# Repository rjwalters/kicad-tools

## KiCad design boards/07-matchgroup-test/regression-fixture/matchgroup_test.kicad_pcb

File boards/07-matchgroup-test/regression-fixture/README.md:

> Historical synthetic routing fixture. These footprints are not an assembled
> product. The working SDRAM redesign is in `../real_design/`. Legacy generators
> remain in the parent directory and default to `../regression-output/`; the
> files here preserve the existing regression witness.

# Match-Group Test Board (Board 07)

Regression testbench for the N-trace match-group routing subsystem
introduced by Epic [#2661](https://github.com/2AMLogic/kicad-tools/issues/2661)
(Phases 1-2).  Demonstrates each match-group scenario the epic was
scoped against (DDR data byte, MIPI CSI lane group, HDMI TMDS lane
group, generic address bus) by routing one or more match-grouped
nets per scenario on a 4-layer JLCPCB tier-1 stackup.

**This is not a working device.**  The source / sink footprints
(QFN-48, BGA-49 simulator, FFC-6, etc.) are synthetic placeholders
chosen to expose realistic escape lengths so the routing algorithm
sees non-trivial group skew to measure / tune.

## Quick Start

```bash
# One-command build (recommended)
kct build boards/07-matchgroup-test

# Or run specific steps
kct build boards/07-matchgroup-test --step schematic
kct build boards/07-matchgroup-test --step pcb
kct build boards/07-matchgroup-test --step route
kct build boards/07-matchgroup-test --step verify

# Run DRC against the committed routed PCB (the fixture in this directory)
kct check boards/07-matchgroup-test/regression-fixture/matchgroup_test_routed.kicad_pcb \
  --mfr jlcpcb \
  --net-class-map boards/07-matchgroup-test/regression-fixture/net_class_map.json
```

## Stackup

4-layer JLCPCB tier-1 (identical to board 06):

| Layer index | KiCad name | Purpose                              |
|-------------|-----------|--------------------------------------|
| 0           | F.Cu      | Signal (escape + outer routing)      |
| 1           | In1.Cu    | GND plane (impedance reference)      |
| 2           | In2.Cu    | PWR plane (+1V2 / +1V8)              |
| 31          | B.Cu      | Signal (optional bottom escape)      |

## Match-Group Scenarios

| Scenario   | Group name           | Members                     | Skew tolerance | Phase features exercised                                                  |
|------------|----------------------|-----------------------------|----------------|---------------------------------------------------------------------------|
| DDR byte   | `DDR_DATA_BYTE_0`    | 9 singles (DQ0-7, DM0) + DQS pair | 0.1 mm    | 1A declaration, 1B tracker, 1C detection, 1D producer, 2E cascade, 2F composition |
| MIPI CSI   | `MIPI_CSI_LANES`     | 3 pairs (CLK, DAT0, DAT1)   | 0.05 mm        | 1A, 1B, 1C, 1D, 2F symmetric serpentine target                            |
| HDMI TMDS  | `HDMI_TMDS_LANES`    | 3 pairs (D0, D1, D2)        | 0.075 mm       | 1A, 1B, 1C, 1D, 2F composition                                            |
| ADDR bus   | `ADDR_BUS`           | 8 singles (A0-A7)           | 0.5 mm         | 1A explicit declaration (also exercises 1C suffix-inference fallback path) |

**4 match groups across 30 paired/grouped nets**.  Combined with
GND/+1V2/+1V8, the board has **33 nets total** --- comparable in
scale to board 06 (26 nets) and well below board 05 (~50 nets).

## Components

| Reference | Description                              | Footprint                                          |
|-----------|------------------------------------------|---------------------------------------------------|
| U1        | QFN-48, 0.8 mm pitch (DDR controller)    | `Package_DFN_QFN:QFN-48-1EP_7x7mm_P0.5mm`         |
| U2        | QFN-48, 0.8 mm pitch (DRAM sink)         | `Package_DFN_QFN:QFN-48-1EP_7x7mm_P0.5mm`         |
| J1        | FFC, 6-pin 1.0 mm pitch (MIPI source)    | `Connector_FFC:FFC_6P_1.0mm`                      |
| U3        | QFN-24, 0.8 mm pitch (MIPI sink)         | `Package_DFN_QFN:QFN-24-1EP_4x4mm_P0.5mm`         |
| J2        | HDMI Type A receptacle (synthetic)       | `Connector_Video:HDMI_A_Receptacle`               |
| U4        | BGA-49 simulator, 1.27 mm pitch          | `Package_BGA:BGA-49_5.0x5.0mm_Layout7x7_P0.5mm`   |
| J3        | 1x9 pin header, 0.1 in pitch (ADDR)      | `Connector_PinHeader_2.54mm:PinHeader_1x09_P2.54mm_Vertical` |
| U5        | QFP-48, 0.8 mm pitch (SRAM-style sink)   | `Package_QFP:LQFP-48_7x7mm_P0.5mm`                |

All sinks placed on F.Cu so all routing happens on the outer signal
layers; GND/PWR planes on inner layers are unencumbered for
impedance reference.

## Per-Group Net Class Declarations

The protocol-specific `NetClassRouting` instances live in
`generate_design.py`:

- `ddr_data_byte_0_net_class()` --- `length_match_group="DDR_DATA_BYTE_0"`,
  `length_match_tolerance_mm=0.1` (DDR commodity tolerance)
- `ddr_dqs_pair_net_class()` --- pair members of DDR group
  + `coupled_routing=True`, `pair_protocol="DDR_DQS_CK"` (UG583 2 ps
  within-pair limit, an error)
- `mipi_csi_net_class()` --- `length_match_group="MIPI_CSI_LANES"`,
  `target_diff_impedance=100`, `pair_protocol="MIPI_DPHY"`
- `hdmi_tmds_net_class()` --- `length_match_group="HDMI_TMDS_LANES"`,
  `target_diff_impedance=100`, `pair_protocol="HDMI_TMDS"`
- `addr_bus_net_class()` --- `length_match_group="ADDR_BUS"`,
  `length_match_reference="A0"` (pace-car semantic)

Within-pair skew is judged against the derived ps budget of the declared
protocol ([guide 09](../../../docs/guides/diff-pairs/09-skew-budget.md)),
with no hand-set `skew_tolerance_mm` cap (Issue #7913): the derived
budget is the only pair skew limit.

`build_net_class_map()` assembles them into a `net_name -> NetClassRouting`
dict that the autorouter (in `route_pcb()`), the JSON sidecar
(`regression-fixture/net_class_map.json`), AND the regression test
(`tests/test_board_07_matchgroup_test.py::test_phase_features_exercised`)
all import.  This ensures test/sidecar/implementation parity.

## Files

Paths below are relative to `boards/07-matchgroup-test/`.  The legacy
generators live in that parent directory; the committed regression
witnesses live here, in `regression-fixture/`.  (`output/` holds the
unrelated real SDRAM-exerciser build --- see `../real_design/`.)

| File                                                   | Description                                           |
|--------------------------------------------------------|-------------------------------------------------------|
| `regression-fixture/project.kct`                       | KCT v1.0 spec (manufacturing/intent metadata)         |
| `generate_schematic.py`                                | Emits the schematic (`matchgroup_test.kicad_sch`)     |
| `generate_pcb.py`                                      | Emits the unrouted PCB + holds NETS / DIFFPAIRS / match-group dicts |
| `generate_design.py`                                   | End-to-end pipeline (schematic + PCB + route + sidecar + DRC); regenerates into `regression-output/` by default, never over the committed fixture |
| `regression-fixture/matchgroup_test.kicad_sch`         | Generated schematic (committed)                       |
| `regression-fixture/matchgroup_test.kicad_pcb`         | Unrouted PCB (committed; the gate's re-route input --- carries #7557's U4 TMDS ball move, see "U4 TMDS ball move" below) |
| `regression-fixture/matchgroup_test_routed.kicad_pcb`  | Routed PCB (committed --- consumed by CI DRC gate)    |
| `regression-fixture/net_class_map.json`                | Sidecar (Phase 3M) consumed by `kct check --net-class-map` |
| `regression-fixture/placement_delta.json`              | Reviewed swap-group pad re-binding (#5537); replayed only via `--placement-delta` |

## DRC Status

The routed PCB is checked against JLCPCB tier-1 rules via:

```bash
kct check boards/07-matchgroup-test/regression-fixture/matchgroup_test_routed.kicad_pcb \
  --mfr jlcpcb \
  --errors-only \
  --net-class-map boards/07-matchgroup-test/regression-fixture/net_class_map.json
```

The `--net-class-map` flag is **mandatory** for the
`match_group_length_skew` rule (Phase 2G #2702) and the diff-pair
rules to fire on the standalone routed PCB --- without the sidecar
they degrade to no-ops (the same trap PR #2692 fixed for diff-pair
rules).

### Initial allowlist budget

Per the curator note on issue #2724, the initial DRC error count is
empirical: route the board, count errors, add ~20% headroom, then
record in `.github/routed-drc-tolerance.yml`.  Phase 3N (#2726) will
tighten iteratively as upstream router improvements land.  (#7367
replaced that count with an identity allowance; see "CI Gate" below.)

## Current targeted repair (2026-09-09)

The committed routed board connects **27/31 signal nets**, including all six
MIPI nets. It remains **partial and unsuitable for manufacturing sign-off**:
`DQ3`, `DQ4`, `TMDS_D0_N`, and `TMDS_D1_N` are open. Native KiCad DRC, with
refilled zones and the original project/rules, reports four unconnected items,
zero other errors, and 31 warnings. `kct check` reports eight errors: those four
opens and the remaining DDR/HDMI pair skew and continuity failures. All three
MIPI pairs and their match group pass the authored electrical checks.

The repair rotates J1 to -90 degrees at the same location, reroutes only MIPI,
and preserves the other copper. MIPI and HDMI width is resolved to 0.225 mm at
the authored 0.100 mm gap (102.3 ohm model, within the authored 100 ohm ±10%
target). DQS remains at its authored 0.150/0.100 mm width/gap. No net mappings,
pair/group constraints, or checks were removed; no waivers were added.

Reproduce the targeted repair in a separate directory:

```sh
uv run python boards/07-matchgroup-test/repair_mipi.py /tmp/board07-repair
```

The script accepts `--input PATH` for a previous routed artifact, sets J1's
absolute orientation, disables the routing cache, runs coupled MIPI routing,
then tunes pair skew and a common six-route length target while enforcing
partner clearances. It saves the full sidecar, tuning results, route log,
native DRC, and full `kct check` report. Exit status 2 reflects the board's
remaining errors. The generator exposes this J1 orientation as an optional
argument; its default placement and routing map stay historical because a fresh
full-board generation/routing run has **not** been measured with this change.
Fixed-gap width sizing is explicitly selected by the repair script;
the committed result comes from the targeted repair of the historical board.
See [the experiment record](../diagnostic-runs/astra-j1-orientation.md).

## Historical routing plateau (before 2026-09-09 repair)

The following measurements describe the previous committed artifact and the
earlier full-board routing recipe. That board connected
**26/31 signal nets** (~83.9% by net count); its
`output/lvs.json` recorded `clean: false` with exactly **5 open
copper mismatches**. The gallery rendered board 07 as `partial`/`lvs`
(the audit was real:
`copper_bound_pad_count: 244`, `copper_vacuous: false` --- cf. #4011).

### The 5 opens

| Net | Pad A | Pad B | Bundle |
|-----|-------|-------|--------|
| `DQ3`         | U1.28 | U2.4  | DDR data byte |
| `DQ4`         | U1.32 | U2.8  | DDR data byte |
| `MIPI_DAT0_N` | J1.4  | U3.4  | MIPI CSI |
| `TMDS_D0_N`   | J2.2  | U4.B2 | HDMI TMDS |
| `TMDS_D1_N`   | J2.5  | U4.B4 | HDMI TMDS |

This is the same set re-measured by the #4049 epic dossier; the older
#3438 thread cited a 3-net subset before the board was re-spun.  Three
verifiers agree on this exact set: `kct net-status --why`,
`output/lvs.json` (`copper_mismatches`), and the KiCad cross-gate
`kicad-cli pcb drc --refill-zones` (5 unconnected pads at the same five
pads).

### Decision: correct HDMI widths while preserving the witness (#5126)

**Recommendation:** permit one explicit, reviewed width correction to this
historical fixture. Retarget existing `TMDS_*` track widths from 0.375 mm to
`HDMI_TMDS_LANES`' declared 0.225 mm, preserving their centerlines, layers,
net assignments and vias. The fixture exists to retain match-group skew geometry
and documented routing defects; a stale width contradicting its own sidecar is
not an additional defect we need to preserve. This does not make the synthetic
board a release artifact or remove its known opens.

The September 12 investigation on #5126 reported matching before/after DRC
error signatures after native refill and an unchanged angle census of 841
segments, including 12 off-angle segments. It also reported that stripping and
rerouting all six TMDS nets reduced their connected count from four to one.
Those are prior experimental results, not acceptance evidence for a future
commit. **A full strip-and-reroute is not proposed.** The present saved fixture
has 0.375 mm segments on the four routed TMDS nets; the two documented open
TMDS nets have no routed segments to retarget.

The alternative is to freeze every byte forever. That preserves the original
hash but leaves the fixture internally inconsistent and teaches readers the
wrong relationship between the sidecar and saved copper. A narrowly documented
exception with measured invariants better preserves the witness's purpose.
The original bytes remain identifiable by SHA256
`ab3a2c2d4aea466f828e540189ac851ddb8c41505c8185be65924ec5ff92a9a6`
and by repository history.

**Implementation gate:** after review of this decision, a separate #5126 PR
must add the width-retarget path to `repair_hdmi.py` and publish its exact
before/after evidence. It must preserve non-TMDS track geometry, all pad/net
identities, vias and authored constraints; `DDR_DQS` is outside this change.
Before promotion, compare native and analyzer pad components and open identities,
not just aggregate counts, and compare DRC error signatures with the original
project/rules and sidecar after native KiCad 10 zone refill. Narrower tracks can
lose a marginal copper contact even when their centerlines are unchanged, so
connectivity must be measured rather than assumed. Retain the original input,
refilled candidate, commands, KiCad identity and hashes for reproduction.
The known-current four-open set above must not be confused with the five-open
historical table, which predates the MIPI repair.

Update `HISTORICAL_WITNESS_SHA256` in `tests/test_fleet_45_census.py` only in the
same implementation commit as the accepted PCB, with a comment citing #5126.
Keep the exact `(841, 12)` angle-census assertion and exercise the match-group
skew checks; do not remove the witness pin or relax its regression gates.
This decision note changes neither PCB bytes nor their hash pin. If independent
review rejects the exception, retain the frozen witness and close #5126 with
that recorded rationale.

### HDMI width correction (2026-09-15, #5126)

The reviewed exception above is applied to **35 width atoms** on the four routed
TMDS nets: `TMDS_D0_P`, `TMDS_D1_P`, `TMDS_D2_N`, and `TMDS_D2_P`, from 0.375 mm
to the sidecar's 0.225 mm. The two open TMDS nets have no track segments.
Every other byte of the saved PCB is unchanged, including segment centerlines,
vias, existing zone fills, and non-TMDS widths. DQS copper is unchanged; this
correction does not establish its agreement with its authored width.

The old PCB SHA256 is recorded in the decision above; the corrected saved PCB is
`fb58581eba53bb9f1dfe33a278fb896b2f08b5f4fc2e82211124d8586ba7aaf0`.
Its hash pin was updated with the PCB, retaining the exact 841-segment,
12-off-angle census. The change is a regression-fixture correction, not a
manufacturing release.

Current-source before/after checks retain the same four open nets and exact
native pad components. Native KiCad 10.0.6 reports four unconnected items,
zero other errors and 31 warnings on each input with native refill enabled.
The current Python checker reports **13 errors, 22 warnings and 12 unique
error rule/net signatures** on both saved inputs, including existing
via-in-pad findings. These are current measurements; the earlier eight-error
account above describes the September 9 check. Match-group checks remain
engaged, and no error severity or allowance was changed.

The [retained component and signature record](hdmi-width-correction-5126.json)
contains the shared exact pad partitions/open identities and all four measured
PCB hashes. Saved and separately refilled before/after copies pass the same
comparisons. Native refills are evidence copies; the committed PCB retains its
original fill bytes so unrelated serialization and geometry remain untouched.

Reproduce from the original fixture in a fresh directory (use a Python with
`pcbnew` for `--native-python`, and a KiCad 10 `kicad-cli` on `PATH`):

```sh
mkdir /tmp/board07-original
git archive bcaf28ad3399d97df5b0d6cfefe8db7856abc689 \
  boards/07-matchgroup-test/regression-fixture | tar -x -C /tmp/board07-original
uv run python boards/07-matchgroup-test/repair_hdmi.py /tmp/board07-hdmi-width \
  --input /tmp/board07-original/boards/07-matchgroup-test/regression-fixture/matchgroup_test_routed.kicad_pcb \
  --native-python python3
```

A completed preservation check reports `validated historical width correction`
in `evidence.json` and exits **2**, retaining the board's existing errors.
Failure raises an error and records `FAILED`; it is not a promotable candidate.
The script retains the original input, byte-minimal candidate, separate native
refills, reports and command logs. It also supports an already-correct input
without further width edits. The current script was verified from the original
fixture; the contact-loss negative test separately proves that a narrower
track losing a real connection is rejected.

### ADDR_BUS retune (2026-10-18, #6730)

`kct retune-lengths --group ADDR_BUS` re-applied the existing match-group tuner
to the saved fixture (only `A4` and `A6` changed; all other nets, vias and
pads are unchanged). ADDR_BUS skew went from **1.0998 mm to 0.0169 mm** (limit
0.5 mm), measured by `kct check` and by `kicad-cli` per-net lengths
(`test_addr_bus_lengths_match_kicad_cli`). The new meanders sit on In1.Cu, so the
zones were refilled with `kct zones fill`; without the refill the stale GND fill
reports six `clearance_segment_zone` errors. Error signatures are otherwise those
of the previous fixture minus the ADDR_BUS skew finding (`diffpair_length_skew` 5,
`via_in_pad` 5, `connectivity` 4). The census is now `(849, 12)` and the PCB
SHA256 is `fdbb69fd1cae5ee76a6a66788feebfed3490f090652df75fdbf04e864f3df83e`.
The input hash and per-net before/after lengths were recorded by the retuner's
provenance record. Earlier sections describe the pre-retune bytes.

### Placement-delta feedback (#4468, epic #3438 Phase 3)

> **Off since #6448.** The recipe now routes on the lattice engine, and the
> loop's probes re-route with the grid negotiated router, so
> `PLACEMENT_DELTA_FEEDBACK` is `False`. The lattice route reaches 31/31,
> so the loop would have nothing to probe. This section records the grid
> recipe's measurements.

The route step runs `kct route --placement-delta-feedback
--placement-delta-feedback-budget 2 --placement-delta-feedback-timeout
600` (wired from the `PLACEMENT_DELTA_FEEDBACK*` constants at the top of
`generate_design.py`).  Since #5266 the surrounding budget contract is
stated as two separate numbers: `--search-timeout 600` bounds each
individual search stage (the initial negotiated pass), while `--timeout`
carries the **hard total** invocation deadline, derived as
`600 + 2x600 + 600 = 2400 s` (one search stage, one probe allocation per
budget unit, and a postprocessing reserve).  The probe allocation does
**not** escape the total deadline -- it is clamped to whatever the total
has left -- so the total must be large enough to contain both probes or
the out-of-process supervisor kills the run mid-probe and leaves only
unverified partial artifacts.  Each iteration classifies the **routed**
board,
translates every `PLACEMENT_BOUND` / `CONGESTION_SATURATED` diagnosis into
one concrete placement delta, applies the top unprobed one, re-routes, and
keeps it only when the re-route **strictly increases the routed-net count
AND does not increase the router's clearance-violation count** ---
otherwise placement, router pads, routes and the routing grid revert
atomically.

**Measured verdict: the reach stays at 26/31, and that is a decision, not
a failure to find anything.**  Solo, seed 42, C++ backend built,
`PYTHONHASHSEED=42`, the loop emits a delta for every one of the 5 open
nets and probes the top two.  The probe-level routed counts are
**host-specific** (see "Host-vs-CI divergence" below); both are recorded:

| # | Probe | Routed (host) | Routed (CI, both runs) | Clearance violations (host) | Verdict |
|---|-------|---------------|------------------------|-----------------------------|---------|
| 0 | `U2` `rotate_180` --- from `DQ3`'s `DE_REVERSE_BUNDLE` verdict | 25 -> **16** | 25 -> **14** | 0 -> **1489** | reverted (reach collapse) |
| 1 | `U3` translate `(-0.77, -1.85)` mm --- from `MIPI_DAT0_N`'s `MOVE_PART` | 25 -> **26** | 25 -> **25** | 0 -> **2** | reverted (host: clearance; CI: no reach gain) |

The `Routed` columns are the loop's internal routed-net counter, whose
baseline at probe time is 25/31; the `26/31 -> 27/31` figures in the
prose below are the same host-measured +1 net expressed as final-artifact
reach (the probe-1 artifact measured 27/31 on that host).

Probe 0 is the informative negative result.  The classifier is **right**
that the DDR byte is reversed at `U2` --- it measures 28/28 facing pad
pairs inverted between `U1` and `U2` --- but a 180-degree rotation is not
the move that fixes it: it de-reverses the pad ORDER while relocating the
whole facing column to the *far* side of the package, so the byte then has
to wrap around a 7x7 mm QFN.  Reach collapses to 16/31.  The
geometrically correct move is a **mirror** of the pad column, which KiCad
expresses only as a layer flip and which the Phase-1 translator therefore
never emits.

Probe 1 is the real finding --- **on the local macOS arm64 host**.  There,
a single bounded 2 mm translate of `U3` **does** close `MIPI_DAT0_N` ---
26/31 -> 27/31 --- but the extra copper it lets into the DDR channel costs
manufacturability.  This is a host-specific measurement, not a universal
one: both independent CI runs (ubuntu-latest, same seed and
`PYTHONHASHSEED`) measured the same probe as routed **25 -> 25** --- no
reach gain --- so on CI the delta is refused for lack of a strict
routed-net increase and the clearance-regression guard never fires.  The
manufacturability cost below was measured on the host's 27/31 artifact:

* two segment-to-pad clearances drop under the jlcpcb floor
  (0.076 mm and 0.094 mm against a 0.102 mm minimum, at the `U1` DDR
  escape), taking blocking DRC from 10 to 13 on the same host; and
* the `ADDR_BUS` length-match tuner, which normally drives that group's
  skew to **0.000 mm**, is left at **11.03 mm** --- a
  `match_group_length_skew` error on the very board that exists to
  exercise that rule.

Shipping it would have required widening
`.github/routed-drc-tolerance.yml`'s board-07 floor from 8 to 13.  Trading
a DRC allowlist widening for one net is not an improvement on a
match-group/DRC testbench, so the loop's acceptance test now requires
*both* a reach gain and no clearance regression, and this delta is
refused.  The refusal is recorded, with its measurements, in
`output/matchgroup_test_routed_placement_delta.json` (the `reverted`
section carries `routed_before` / `routed_after` and `revert_reason`) so
the decision is auditable rather than invisible.

**The acceptance test is *relative*, and #4770 measured what that costs.**
`PlacementDeltaFeedbackLoop.run_delta` keeps a delta on
`new_count > pre_count` --- a comparison against the reach the loop
currently holds, not against an absolute floor.  So anything that
*depresses* the initial negotiated pass's reach also lowers the bar this
probe has to clear.  Issue #4770's A/B is the worked example: with the
relief-rescue sub-search bound switched from its 10 s wall clock to the
deterministic per-net expansion cap (#4730's withdrawn flip), the
negotiated pass completes 2 rip-up iterations instead of 5 and enters the
loop at 24/31 instead of 26/31 --- and *on CI* this same `U3` translate
then measures 23 -> 27, clears the gate, and is **kept**, taking blocking
DRC from 8 to 13 with exactly the 0.076 / 0.094 mm `U1`-escape clearances
and the 11.03 mm `ADDR_BUS` skew described above.  The `+1 net` in that
measurement is this delta, not a router improvement.  Full journal:
`diagnostic-runs/README.md`, section "Deterministic relief-rescue bound:
A/B measurement (#4770)".

Two useful side effects of running the loop, both measured on the same
host:

* the delta artifact is emitted on **every** run, so the classifier's
  per-net proposal for each open net is a build output rather than a
  one-off investigation; and
* blocking DRC on the shipped artifact measures **8** (equal to the
  committed allowlist floor) versus **10** for a loop-off local regen ---
  the loop's atomic revert now also rebuilds the routing grid, which the
  post-loop optimize/DRC-nudge stages read.

The shipping budget is **2**: probe 0 is the classifier's top-ranked rung
and probe 1 is the one that is only marginally short of acceptable, so if a
future router change removes those two clearances the loop will take the
net automatically.  A direct consequence: `DQ4`, `TMDS_D0_N` and
`TMDS_D1_N` are **unprobed-by-budget, not unroutable** --- the loop
proposes a delta for each of them (all proposals are recorded in the
delta artifact; CI logs `Deltas proposed: 10`), but the budget of 2 is
consumed by `DQ3`'s and `MIPI_DAT0_N`'s probes before those three are
ever tried.  Their `CONGESTION_SATURATED` / `PLACEMENT_BOUND` verdicts in
the table below describe why the *router* leaves them open at the current
placement; no placement delta for them has been probed and refused.  Each
budget unit costs one complete board-07 re-route; the whole route step
measures **27m05s** locally against ~16 min for the loop-off recipe.

#### Host-vs-CI divergence (probe-level only)

The probe-level routed counts above are host-dependent even at a fixed
seed.  Same code, `--seed 42`, `PYTHONHASHSEED=42`:

* local macOS arm64 host: probe 0 routed `25 -> 16`, probe 1 routed
  `25 -> 26` (reverted for clearance);
* CI ubuntu-latest: probe 0 routed `25 -> 14`, probe 1 routed `25 -> 25`
  (reverted for no reach gain) --- reproduced **bit-for-bit across two
  independent CI runs** on different head SHAs (PR #4556; run
  `30680605924` and its predecessor).

The *decisions* and the final state agree everywhere: 10 deltas proposed,
0 kept, exit `pd_reverted`, 26/31 reach, the identical 5-net open set,
and blocking DRC 8 at the committed floor.  Only the probe-level
narrative diverges.  This is the same honesty hazard as board-06's
run-to-run nondeterminism (#4536), on a cross-host axis: future
threshold or known-open decisions for this board should be made against
the CI numbers.

#### Mirror probe (#4560) --- first measurement

`DE_REVERSE_BUNDLE` now proposes `kind="mirror"` (a KiCad-semantics
layer flip of `U2` about its own anchor) instead of `rotate_180`, so
probe 0 of a fresh run is the mirror.  The structural diagnosis is
unchanged and still correct --- 28/28 facing pad pairs invert between
`U1` and `U2`, and a flip is the only orientation move that can
un-reverse a mirrored pin order (rotate_180 preserves chirality).

First measurement, **host-qualified per the divergence note above**
(macOS arm64, solo, `--seed 42`, `PYTHONHASHSEED=42`):

* probe 0 `U2` **mirror**: routed `25 -> 23`, clearance `0 -> 69`,
  reverted.  The flip moves `U2`'s pad column to `B.Cu`, which
  un-reverses the bundle *ordering* but relocates the entire DDR escape
  problem to the back side, where the routed baseline's copper and the
  skipped power fanout already live --- reach drops and the
  clearance-regression gate fires.  For calibration: the rotate_180 it
  replaces measured `25 -> 16` on this host (`25 -> 14` on CI), so the
  mirror is the better probe of the two, but neither survives.
* probe 1 `U3` translate: routed `25 -> 26`, clearance `0 -> 2`,
  reverted --- the same host-only marginal keep/refuse case documented
  above, refused again by the clearance gate.

Final state is bit-identical in shape to the committed baseline: 10
deltas proposed, 0 kept, exit `pd_reverted`, 26/31 reach, the identical
5-net open set (`DQ3`, `DQ4`, `MIPI_DAT0_N`, `TMDS_D0_N`, `TMDS_D1_N`).
The atomic revert (placement + router pads + routes + grid, now
layer-aware) restored the board exactly; the delta artifact records both
refusals with `routed_before`/`routed_after` and `revert_reason`.  CI
numbers for the mirror probe should be recorded from this change's
board-07 e2e job when available.

### Netlist write-back from a committed delta (#5537, Epic #5511 Phase 2b)

`regression-fixture/placement_delta.json` is a **committed, reviewed**
placement-delta artifact carrying the declared `DDR_BYTE0` swap group's
crossing-minimising pad re-binding for `U2` (`crossings_before: 28` ->
`crossings_after: 0`, measured by the #5522 proposer against
`matchgroup_test_routed.kicad_pcb` + `net_class_map.json`).  It is the
same `{pad_number: new_net_name}` payload
`kct net-status --why --format json` reports; the deltas were promoted
from the classifier's `proposed` list into the artifact's `applied`
section by that review, and **nothing replays `proposed` automatically**.

The recipe consumes it via `PlacementDelta.from_dict` and applies the
`pad_map` to **both** generated views *before* routing, so the swap
survives a full regeneration and the schematic/PCB still agree pad-for-pad
(a one-sided swap would surface as an LVS mismatch on every re-bound pad):

```sh
uv run python boards/07-matchgroup-test/generate_design.py /tmp/board07-swap \
  --placement-delta boards/07-matchgroup-test/regression-fixture/placement_delta.json
```

The run prints the change report (target, kind, source action, the
`crossings_before`/`crossings_after` evidence and every `pad -> net`
binding) and writes it to `placement_delta_applied.txt` next to the
regenerated artifacts.  `generate_schematic.py` and `generate_pcb.py`
accept the same flag for a single-view regen; `--step route` does not
(it consumes an already-generated PCB and says so).

**Opt-in only.** With the flag absent every generated byte is what it was
before #5537, so the committed witnesses in this directory are unaffected
and are **not** regenerated by that change: the historical open set, the
routed-DRC allowlist floor and the angle-census pin below all still
describe the board that is committed here.  Re-binding `U2`'s DQ pads
changes which nets the router must reach, which would invalidate every one
of those measurements, so promoting a swapped board to the committed
fixture is a separate, separately-measured decision.

The re-binding touches only the eight **declared** `DDR_BYTE0` members
(DQ0-DQ7 on `U2` pads 1-4 / 8-11).  `DM0`, `DQS_P` and `DQS_N` are
`DDR_DATA_BYTE_0` match-group siblings that are deliberately **not**
declared swappable and stay fixed, and no `ADDR_BUS` net is touched at
all.

### Fresh per-net verdict (`kct net-status --incomplete --why`)

Measured on the committed routed PCB and reproduced by a from-scratch
seed-42 re-route (`PYTHONHASHSEED=42 generate_design.py --step route
--seed 42`), which lands on the **identical** 5-open set and the same
classification:

```
Stuck signal nets: 5
  ESCAPE_BLOCKED:       0
  CONGESTION_SATURATED: 2
  BUDGET_STARVED:       0
  PLACEMENT_BOUND:      3
  POUR_DISCONTINUOUS:   0
```

| Net | Verdict | Evidence |
|-----|---------|----------|
| `TMDS_D0_N`   | `CONGESTION_SATURATED` | pad reachable (360 deg lane) but boxed in by committed strict copper (nearest blocker 1.000mm); ripping it would strand `TMDS_D0_P`, `TMDS_D1_P` (1:1 trade) |
| `TMDS_D1_N`   | `CONGESTION_SATURATED` | boxed in (nearest blocker 0.975mm); rip would strand `TMDS_D1_P`, `TMDS_D2_P` (1:1 trade) |
| `DQ3`         | `PLACEMENT_BOUND` | dense cluster (24 foreign obstructions, nearest strict blocker 0.800mm) --- a part must move |
| `DQ4`         | `PLACEMENT_BOUND` | dense cluster (30 foreign obstructions, nearest strict blocker 0.047mm) --- a part must move |
| `MIPI_DAT0_N` | `PLACEMENT_BOUND` | dense cluster (39 foreign obstructions, nearest strict blocker 0.800mm) --- a part must move |

The key signal: **0** nets are `BUDGET_STARVED` (which more router
iterations/wall-clock would fix) or `ESCAPE_BLOCKED` (which corridor
reservation would fix).  Every stuck net is either the diagnostic's own
"a part must move" `PLACEMENT_BOUND` verdict (3/5) or a
`CONGESTION_SATURATED` 1:1 trade (2/5) where ripping the stuck net simply
strands its diff-pair partner --- the N-1 invariant #3438 first
documented.

### What was attempted this pass (v0.16.0 router)

A fresh seed-42 route with the current v0.16.0 router (region-bounded
routing, ampacity net-class, and the post-#4049 hardening all now on
`main`, C++ backend built) was run end-to-end.  The negotiated router's
relief-rescue phase explicitly reported **`Relief rescue resolved 0/5
net(s)`**: for each stuck net it either found no relief path, or found a
path that displaced victims it could not re-land (rolled back under the
no-net-loss guarantee).  The best-so-far routed state (26/31, 0 clearance
violations, 0 overflow) is identical in open-set to the committed
artifact, so the committed artifact remains the shipping truth and is
left unchanged (regen diverges only in trace geometry/UUIDs, not in which
nets close).

### Track A bundle-plan allocator — measured seed-42 verdict (#4257, A4)

Track A (#4252) built the "joint bundle corridor allocation" fix named
below as the genuine remedy for the `CONGESTION_SATURATED` TMDS 1:1
trades: an **atomic diff-pair rip-up/relief transaction** (A2, #4255) so a
committed "P-routed / N-stranded" state is unrepresentable, plus a
**discrete `BundlePlan` allocator with HARD (foreign-net keep-out) per-member
lane reservation** (A3, #4256).  A4 (#4257) wired both through all three
negotiated entry points (`route_all`, `route_all_negotiated`,
`TwoPhaseRouter`) behind the default-OFF `--bundle-river-planner`
(`enable_bundle_river_planner`) flag and ran the board-07 acceptance gate.

**Honest outcome: the TMDS opens do NOT close; the residual is
placement-bound.**  A solo seed-42 A/B on one host (C++ backend built,
`--deterministic-budget`, `PYTHONHASHSEED=42`) measured:

| Run | Reach | Open set |
|-----|-------|----------|
| flag **OFF** (default / shipping) | **26/31** | `DQ3`, `DQ4`, `MIPI_DAT0_N`, `TMDS_D0_N`, `TMDS_D1_N` |
| flag **ON** (`--bundle-river-planner`) | **23/31** | the 5 above **+** `MIPI_CLK_N`, `TMDS_D0_P`, `TMDS_D1_P` |

The reason is the load-bearing A3 finding, now re-confirmed against the
committed placement: the allocator returns the HDMI TMDS bundle
**FEASIBLE with 6 trivial in-order OUTER lanes and 0 via-hops** — the two
facing rows (J2 / U4) carry `D0..D2` co-oriented, so there is **no
forced-crossing contention for the allocator to resolve**.  Reserving the
resulting HARD lanes (12 keep-out lanes / 3780 grid cells across the TMDS
and MIPI bundles) therefore does not open the stuck TMDS N-legs; it only
walls off cells the congested single-ended negotiator needed, stranding
the *partners* (`TMDS_D0_P`, `TMDS_D1_P`, `MIPI_CLK_N`) — a **regression**,
not a gain.

Conclusion: `TMDS_D0_N` / `TMDS_D1_N` are **`PLACEMENT_BOUND`**, not
coupling-contention-bound.  No HARD-lane reservation closes them; the
residual is the same "a part must move" limit as `DQ3` / `DQ4` /
`MIPI_DAT0_N`, tracked under **Track B / #4253** (placement rework).  The
board-07 reach is therefore **unchanged at 26/31** and **the committed
routed artifact is not refreshed** (the flag stays OFF by default and
flag-off is byte-identical to pre-A4 `main`).  Track A still ships its
real deliverable — the general, verified coupled-bundle capability (atomic
pair transaction + discrete allocator + HARD lane reservation, exercised
end-to-end from all three negotiated entry points in
`tests/router/test_bundle_plan_three_path_integration.py`) — available for
future geometries where a bundle *is* crossing-contended, behind the
default-OFF flag so production routing is unperturbed.

### Required class of fix (follow-up, out of scope here)

None of the four gaps is a knob the single-ended negotiated router can
turn today:

- **`PLACEMENT_BOUND` (DQ3, DQ4, MIPI_DAT0_N)** --- the diagnostic's
  verdict is literally "a part must move."  Resolving these requires a
  **placement rework** of the U1/U2/U3/U4/J1/J2 cluster, a separate and
  larger design change (out of scope per this board's charter; see
  #4049).
- **`CONGESTION_SATURATED` 1:1 trades (TMDS_D0_N, TMDS_D1_N)** ---
  ripping the stuck net strands its pair partner.  The genuine fix is
  **joint bundle corridor allocation** (route the whole HDMI/DDR/MIPI
  bundle's escape channel as a coupled group rather than net-by-net),
  the crossing-aware river-routing planner explored and deferred in
  **#3673**, and the CoupledPathfinder budget rework noted under #4049.

The exhaustive knob matrix (iterations, seed, monte-carlo,
differential-pairs, micro-via-in-pad, grid 0.1, two-pass pre-route,
targeted-ripup) was already swept to exhaustion in **#3438** without
reaching 31/31; the 11-net DDR bundle fails 2/11 *alone* on an empty
board.  The board-07 router epic **#4049** re-confirmed this and closed
at plateau.  This pass (#4235) re-validates that verdict against
v0.16.0.  The joint-corridor + placement-rework follow-up is tracked in
**#4243**.

Gap 2 (diff-pair length-skew / routing-continuity quality errors on the
pairs that *are* routed --- DQS/MIPI_CLK/MIPI_DAT1/TMDS_D2) is a
different root cause (pairs routed as independent single-ended traces),
tracked under #4049, and is deliberately **not** touched here.

## Phase 3 Dependency: #2723 (`--length-match-groups`)

The `apply_match_group_tuning` orchestrator + `--length-match-groups`
CLI flag are introduced by **Phase 3H (#2723)** and have NOT yet
landed on `main` at the time of this board's scaffolding.

What works today (Phases 1A/1B/1C/1D + 2.5G):

- `length_match_group` net-class field is declared on every group
- `detect_match_groups` consumes the declarations during routing
- `_finalize_routing` populates `MatchGroupTracker` with measured
  per-group skew (post-route)
- `match_group_length_skew` DRC rule fires when the sidecar JSON
  is loaded into `kct check`

What is deferred until #2723 lands:

- Group-level meander insertion to actively REDUCE skew (only
  measurement happens today)
- AC#7's "post-pass skew strictly less than pre-pass skew" check
  for the DDR data byte (today's pre-pass and post-pass skews
  are identical because no tuning step runs)

Status update: #2723 has since landed and is closed. `route_pcb` in
`../generate_design.py` now passes `--length-match-groups` (#3098), so
the deferral described above is historical. The `# TODO Phase 3H
(#2723)` comment that remains there asks only to verify that the flag
consumes the `net_class_map.json` sidecar.

## CI Gate (Phase 3N, #2726)

This board is consumed by the **Phase 3N CI gate** (issue #2726),
which lives at `.github/workflows/ci.yml::matchgroup-routing-regression`.
The gate is a sibling of the `diffpair-routing-regression` job (board
06) and runs on every PR to `main`.  Contract:

1. Re-routes board 07 from scratch with
   `python boards/07-matchgroup-test/generate_design.py --step route --seed 42`.
2. Asserts every blocking DRC finding is listed **by identity** (rule +
   pair, net or match group, each with an open tracking issue) in
   `MATCHGROUP_FIXTURE_ALLOWED_FINDINGS` / `MATCHGROUP_ALLOWED_GROUPS` in
   `scripts/ci/check_matchgroup_coverage.py`, and that every listed entry
   still fires (a fixed finding fails the gate as stale until its entry
   is deleted).  The board has no entry in
   `.github/routed-drc-tolerance.yml`, so the count of blocking findings
   *outside* the allowance must be 0
   ([#7367](https://github.com/2AMLogic/kicad-tools/issues/7367); the
   old count, ratcheted 35 -> 14 -> 9 -> 8, let a new finding hide
   behind a fixed one).  Advisory `connectivity` is not blocking; reach
   is gated by item 4.
   <!-- kct:doc-pin drc-tolerance boards/07-matchgroup-test/regression-fixture/matchgroup_test_routed.kicad_pcb = 0 -->
   The claim above is machine-checked by `kct check --only doc_drift`
   (issue #4540): ratcheting the yml without updating this README
   trips `doc_drift_stale_pin`.
3. Asserts the `match_group_length_skew` DRC rule was actually
   exercised --- i.e., `rules_checked_by_rule["match_group_length_skew"] >= 1`
   in the `DRCChecker` summary.  Without this assertion a regression
   that disables match-group detection (e.g., a future change that
   breaks `derive_group_skew_data` or unwires `length_match_group`
   from the net classes) would silently produce a 0-violation report
   and hide the defect.
4. Asserts signal reach (Issue #7319): at least `REQUIRED_SIGNAL_REACH`
   (31 since #7557) of the 31 non-pour nets are complete per `NetStatusAnalyzer`,
   the same counter board 06's gate uses.  Below it the gate exits 2 and
   names the open nets.  The committed 27/31 routed artifact in this
   directory is below the contract on purpose; it is the witness that
   the assertion bites (`--skip-route` against it fails).

### Lattice recipe (Issue #6448, slice 1)

The recipe routes with `--route-engine lattice --strategy basic` (plus the
unchanged `--differential-pairs`, `--tighten-diffpair-gap`,
`--length-match-groups`, `--deterministic-budget`, seed 42). The grid
`--strategy negotiated` run and its placement-delta loop are gone. Measured on
main `1388d4190` (native build 65, `PYTHONHASHSEED=42`, pinned KiCad 10.0.6
image, `--refill-zones`):

| check | lattice recipe |
|---|---|
| pairs coupled | 7/7 |
| signal reach / copper-LVS | 31/31; 0 shorts / 0 opens over 244 pads |
| pair skew | DQS 0.260 mm (1.454 ps of 2.00 ps); MIPI_CLK/DAT0/DAT1 and TMDS_D0/D1/D2 0.000 mm |
| group skew | DDR_DATA_BYTE_0 0.001 mm; MIPI_CSI_LANES 0.000 mm; HDMI_TMDS_LANES 0.000 mm |
| `kct check --mfr jlcpcb` | 0 errors |
| kicad-cli DRC | 0 errors, 0 unconnected; the same 24 warnings as grid |
| `check_board07_diffpair_baseline.py` | copper_safety 0, opens 0, skew_out_of_range 0 |
| `check_matchgroup_coverage.py --seed 42` | exit 0, 0 unallowed errors |

The route step runs about 1 min, against about 27 min for the grid recipe.
Its derived `--timeout` drops from 2400 s to 1200 s because there are no
probe allocations.

### Re-route reach (seed 42, Issue #7319)

The gate's seed-42 re-route reaches **31/31** since #7557 (see "U4 TMDS
ball move" below); before it, **30/31** (`TMDS_D0_N` open) with 0
placement-delta probes.  #7163 briefly dropped it to 29/31: the DDR strobe
pair carried no impedance target, so the router synthesized 100 ohm from
the validator's `.*_[PN]$` default and re-solved the DQS **width** at the
0.1016 mm manufacturer gap floor -- 0.175 mm under the #7163 field solve
(0.225 mm before it).  DQ0 went open and a `U2 mirror` probe tripled the
gate's wall time.  `DDR_DQS` now declares the 100 ohm target and is sized
like MIPI/HDMI (0.225 mm held, 0.135 mm gap, 99.7 ohm).  Measured
back-to-back on one host (C++ backend, `PYTHONHASHSEED=42`):

| run | iteration-0 | final | probes | channel phase | gate wall |
|---|---|---|---|---|---|
| `bd3c8fb10` (pre-#7163) | 30/31 | 30/31 | 0 | 507 s | 992 s |
| DQS sized (#7319) | 30/31 | 30/31 | 0 | 358 s | 702 s |

#### Blocking reason for `TMDS_D0_N` (Issue #7554, re-measured on 30/31)

Re-measured on the 30/31 layout (`main` @ `fd8a974cd`, C++ backend,
`PYTHONHASHSEED=42`, `generate_design.py <dir> --step all --seed 42`).
The negotiated router's access-loss witness names the cause:

```
TMDS_D0_N sealed in at iteration[1]: U4.B2 has no legal exit, closed by
TMDS_D1_P, TMDS_D2_P, U4.A2, U4.B1, U4.B3, U4.C2
```

Targeted rip-up (`TMDS_D0_P`, `TMDS_D1_P/N`, `TMDS_D2_P/N`) and two
relief-rescue rounds resolved 0/1: the victims cannot be re-landed.  The
pad is enclosed by neighbouring BGA pads plus the committed escapes of two
other TMDS legs, so the open is escape-bound (a 1:1 trade), not
budget-starved.  No router knob closes it; it needs a placement change or
joint TMDS escape-corridor allocation (#3673), tracked in #7557.  The run
was cut at a 600 s wall-clock cap, after the witness, so no final reach
figure was taken; the 30/31 figure above is unchanged.

#### U4 TMDS ball move (Issue #7557): 30/31 -> 31/31

U4 is a synthetic BGA-49 sink, so which ball carries which TMDS leg is a
free design choice.  The classifier offers no U4 delta for this open
(`classify_stuck_nets_from_pcb`: `CONGESTION_SATURATED`,
`co_oriented_bundle`, `move_part` / `accept_plateau` only, empty
`proposed`), so the candidates were measured directly.  Each was replayed
as a U4 `pad_map` through `generate_design.py <dir> --step all --seed 42
--placement-delta <file>` (C++ backend, `PYTHONHASHSEED=42`, `main` @
`b77661d2f`); the vacated row-B balls become `GND`:

| U4 TMDS balls (D0_P, D0_N, D1_P, D1_N, D2_P, D2_N) | reach | result |
|---|---|---|
| B1..B6 (baseline, row B, one ring in) | 30/31 | `TMDS_D0_N sealed in ... U4.B2 has no legal exit` |
| `{A2: TMDS_D0_N, B2: GND}` only (2026-10-20 builder note) | 30/31 | seal-in follows the net to `U4.A2` |
| A1..A6 (outer row A, top edge) | 30/31 | `U4.A2 has no legal exit, closed by TMDS_D1_P, TMDS_D2_P, U4.A1, U4.A3, U4.B2`; copper-LVS also opens `+1V2` (U4.C2) and `+1V8` (U4.D2) |
| **A1..F1 (outer column 1, J2-facing, top to bottom)** | **31/31** | copper-LVS clean, 0 unconnected; 748 segments, 28 vias, 983.52 mm |
| G1..B1 (outer column 1, bottom to top) | 31/31 | copper-LVS clean; 757 segments, 30 vias, 985.60 mm |

Column 1 faces J2 (which sits 25 mm to the left at the same y), so every
leg leaves the package straight toward the connector without threading
the row-A GND balls.  A1..F1 is committed (fewer vias, shorter) as a
recipe constant in `generate_pcb.py` / `generate_schematic.py` (both
generators, so the netlist stays consistent and CI needs no
`--placement-delta`), and the same 11-pad re-binding is applied to
`matchgroup_test.kicad_pcb` here so this gate's re-route sees it.  The
committed schematic and routed PCB in this directory stay the legacy
witness (the routed one is the 27/31 artifact item 4 relies on).

Before / after on the seed-42 re-route (pinned kicad-cli 10.0.6 via
`KCT_KICAD_DOCKER=1`; two consecutive `--step all` runs produced
byte-identical routed PCBs):

| | before (B1..B6) | after (A1..F1) |
|---|---|---|
| signal reach | 30/31 | 31/31 |
| copper-LVS | 1 open (`TMDS_D0_N`) | clean |
| native DRC (`--refill-zones`, errors) | 7 `skew_out_of_range` + 1 unconnected | 7 `skew_out_of_range` + 0 unconnected |
| `kct check` blocking (with sidecar) | 6 pair skew, 4 impedance, 2 group skew, 1 connectivity | 7 pair skew, 6 impedance, 3 group skew |

The new `kct check` findings are on the newly routed pair and the group
it completes, in rule families already tracked: `TMDS_D0` pair skew
(4.149 mm, P 2 vias / N 0, #7619), `TMDS_D0_P/N` impedance (125.2 ohm,
#7349) and `HDMI_TMDS_LANES` group skew (7.723 mm, #7550).  They are
listed by identity in `check_matchgroup_coverage.py`.  `TMDS_D1` pair
skew fell 4.968 -> 1.584 mm (no longer via-imbalanced, re-pointed from
#7619 to #7550); `TMDS_D2` moved 0.730 -> 0.833 mm.  No other net's findings changed.

The committed `net_class_map.json` here still describes the committed
routed artifact (DQS 0.150/0.100, MIPI/HDMI gap 0.100); it is regenerated
with that artifact under #6730 / #7283, not by the gate.

### Interpreting a failure

- **`Match-group rule(s) NOT exercised`** -- the rule short-circuited
  because no declared groups were detected with measurable skew.
  Likely causes: `length_match_group` field unwired from one or more
  net classes in `build_net_class_map`, `derive_group_skew_data`
  broken (e.g., `detect_match_groups` returning empty), or the
  routed PCB has no traces matching any declared group's members.
  See `src/kicad_tools/validate/match_group_skew.py` and
  `src/kicad_tools/validate/rules/match_group_length_skew.py` for
  the engagement conditions.
- **`Reach regression on re-routed ...`** -- fewer signal nets
  complete than `REQUIRED_SIGNAL_REACH` in `generate_design.py`.  The
  message names the open nets.  Measure which routing input changed
  (class geometry in the sidecar, per-net copper widths) before
  lowering the contract.
- **`Errors outside the identity allowance`** / **`DRC errors
  detected on re-routed ...`** -- the routing algorithm produced a
  finding on a rule/identity the allowance does not list.  Fix the
  router regression; an accepted, separately-tracked defect is listed
  by identity with its open tracker, never by count.
- **`Stale identity allowance`** -- a listed finding no longer fires:
  delete its entry.
- **Job times out (> 10 min)** -- routing wall-clock crept above
  the budget.  File a follow-up to move the gate to a nightly
  schedule per Epic #2661's runtime guidance.

### Reproducing the gate locally

```bash
# Full re-route + check (CI semantic, ~30-90s on a developer laptop)
python scripts/ci/check_matchgroup_coverage.py boards/07-matchgroup-test --seed 42

# Fast iteration against the committed routed PCB (skips the route step)
python scripts/ci/check_matchgroup_coverage.py boards/07-matchgroup-test \
  --seed 42 --skip-route
```

### Branch-protection (admin action required post-merge)

Per the precedent set by `diffpair-routing-regression` (PR #2679),
adding `Match-Group Routing Regression` to the list of *required*
status checks on `main` is a separate repo-admin action in GitHub
Settings -> Rules -> Rulesets.  Until that flip happens the job
runs on every PR but is advisory --- its failure does not block
the merge button.

## Out of Scope

Per issue [#2724](https://github.com/2AMLogic/kicad-tools/issues/2724)
Scope (out):

- **No new router / validate features.** This board EXERCISES
  Phases 1-2; it doesn't add new router logic.  Missing-feature
  gaps file separate issues under #2661.
- **No reference circuits.** No actual DDR controller, no real
  MIPI camera. Connector / package -> breakout footprint is enough.
- **No 5th scenario** (USB 3.0, SDIO, etc.). Scope is fixed at 4.
- **No CI matrix wiring.** Phase 3N (#2726) does that wiring.
- **No modification of boards 01-06.** Purely additive.

## Related Issues

- Epic: [#2661](https://github.com/2AMLogic/kicad-tools/issues/2661) (N-trace match-group routing subsystem)
- This issue: [#2724](https://github.com/2AMLogic/kicad-tools/issues/2724) (Phase 3L scaffolding)
- Blocked by: [#2723](https://github.com/2AMLogic/kicad-tools/issues/2723) (Phase 3H CLI flag + orchestrator)
- Blocks: [#2726](https://github.com/2AMLogic/kicad-tools/issues/2726) (Phase 3N CI integration)
- Documentation: Phase 3M will cite this board's `project.kct` + net-class declarations as canonical examples.

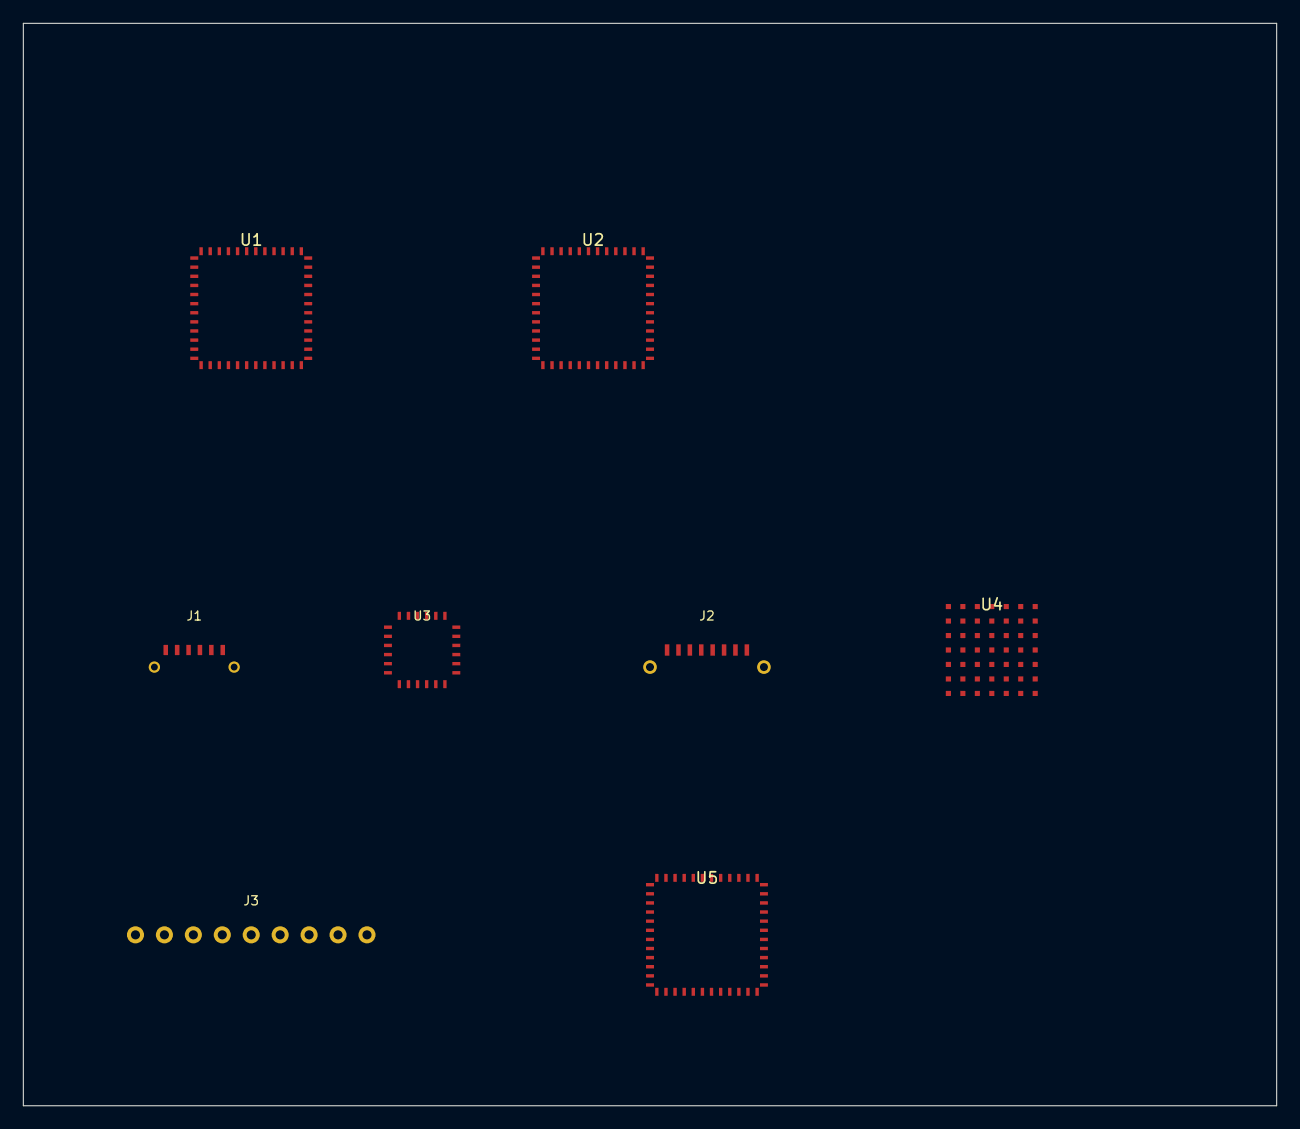
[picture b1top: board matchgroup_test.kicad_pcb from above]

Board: 4 copper layers, 110.0 x 95.0 mm, 8 parts (0 on the bottom side), 34 nets, no tracks yet.

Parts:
J1: FFC6_MIPI; FFC_6P_1.0mm
J2: HDMI19; HDMI_A_Receptacle
J3: ADDR_HDR; PinHeader_1x09_P2.54mm_Vertical
U1: QFN48_DDR_CTRL; QFN-48-1EP_7x7mm_P0.5mm
U2: QFN48_DRAM; QFN-48-1EP_7x7mm_P0.5mm
U3: QFN24_MIPI; QFN-24-1EP_4x4mm_P0.5mm
U4: BGA49_HDMI; BGA-49_5.0x5.0mm_Layout7x7_P0.5mm
U5: QFP48_SRAM; LQFP-48_7x7mm_P0.5mm

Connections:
+1V2: U1.12, U1.36, U2.12, U2.24, U3.18, U4.C2, U4.E6, U5.24
+1V8: U1.1, U2.36, U3.12, U4.C3, U4.C4, U4.C5, U4.C6, U4.D2, U4.D3, U4.D4, U4.D5, U4.D6, U4.E2, U4.E3, U4.E4, U4.E5, U5.12, U5.36
A0: J3.2, U5.1
A1: J3.3, U5.2
A2: J3.4, U5.3
A3: J3.5, U5.4
A4: J3.6, U5.5
A5: J3.7, U5.6
A6: J3.8, U5.7
A7: J3.9, U5.8
DM0: U1.29, U2.5
DQ0: U1.25, U2.1
DQ1: U1.26, U2.2
DQ2: U1.27, U2.3
DQ3: U1.28, U2.4
DQ4: U1.32, U2.8
DQ5: U1.33, U2.9
DQ6: U1.34, U2.10
DQ7: U1.35, U2.11
DQS_N: U1.31, U2.7
DQS_P: U1.30, U2.6
GND: J1.M1, J1.M2, J2.3, J2.6, J2.S1, J2.S2, J3.1, U1.2, U1.3, U1.4, U1.5, U1.6, U1.7, U1.8, U1.9, U1.10, U1.11, U1.13, U1.14, U1.15, U1.16, U1.17, U1.18, U1.19, U1.20, U1.21, U1.22, U1.23, U1.24, U1.37, U1.38, U1.39, U1.40, U1.41, U1.42, U1.43, U1.44, U1.45, U1.46, U1.47, U1.48, U2.13, U2.14, U2.15, U2.16, U2.17, U2.18, U2.19, U2.20, U2.21, U2.22, U2.23, U2.25, U2.26, U2.27, U2.28, U2.29, U2.30, U2.31, U2.32, U2.33, U2.34, U2.35, U2.37, U2.38, U2.39, U2.40, U2.41, U2.42, U2.43, U2.44, U2.45, U2.46, U2.47, U2.48, U3.7, U3.8, U3.9, U3.10, U3.11, U3.13, U3.14, U3.15, U3.16, U3.17, U3.19, U3.20, U3.21, U3.22, U3.23, U3.24, U4.A2, U4.A3, U4.A4, U4.A5, U4.A6, U4.A7, U4.B2, U4.B3, U4.B4, U4.B5, U4.B6, U4.B7, U4.C7, U4.D7, U4.E7, U4.F2, U4.F3, U4.F4, U4.F5, U4.F6, U4.F7, U4.G1, U4.G2, U4.G3, U4.G4, U4.G5, U4.G6, U4.G7, U5.9, U5.10, U5.11, U5.13, U5.14, U5.15, U5.16, U5.17, U5.18, U5.19, U5.20, U5.21, U5.22, U5.23, U5.25, U5.26, U5.27, U5.28, U5.29, U5.30, U5.31, U5.32, U5.33, U5.34, U5.35, U5.37, U5.38, U5.39, U5.40, U5.41, U5.42, U5.43, U5.44, U5.45, U5.46, U5.47, U5.48
MIPI_CLK_N: J1.2, U3.2
MIPI_CLK_P: J1.1, U3.1
MIPI_DAT0_N: J1.4, U3.4
MIPI_DAT0_P: J1.3, U3.3
MIPI_DAT1_N: J1.6, U3.6
MIPI_DAT1_P: J1.5, U3.5
TMDS_D0_N: J2.2, U4.B1
TMDS_D0_P: J2.1, U4.A1
TMDS_D1_N: J2.5, U4.D1
TMDS_D1_P: J2.4, U4.C1
TMDS_D2_N: J2.8, U4.F1
TMDS_D2_P: J2.7, U4.E1

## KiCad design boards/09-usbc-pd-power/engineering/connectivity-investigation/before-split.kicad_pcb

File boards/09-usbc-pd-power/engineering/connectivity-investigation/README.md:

# Board 09 connectivity disagreement

Diagnostic files are not manufacturing artifacts. `before-split.kicad_pcb`
is the fully routed board before explicit mid-track junction splitting.
`before-split-native-drc.json` records zero native violations and opens;
`before-split-copper-lvs.json` records five false opens on +3V3 and PMOS_SOURCE.
Splitting those segments at existing branch/pad centers changed the buffered
trace union by exactly 0.0 mm² on every net/layer (Shapely comparison).
The canonical `../../output/copper-lvs.json` passes with 153 bound pads.
Tracked in https://github.com/2AMLogic/kicad-tools/issues/5060.

To rerun, copy the canonical output project, schematic, and local libraries
to a temporary directory; replace its PCB with this snapshot, keeping the
`usbc_pd_power` basename. Refill using `kicad-cli pcb drc --refill-zones
--save-board --format json --output drc.json usbc_pd_power.kicad_pcb`.
Use `compare_copper_netlist(schematic_path, pcb_path)` from
`kicad_tools.lvs.copper_lvs` for the physical comparison.

The canonical strict `output/net-status.json` separately reports four USB
GND pads unconnected despite native zero opens and two filled inner GND
planes. Earlier capacitor array contacts also triggered two false opens;
explicit pad-center stubs removed those. USB shield-annulus trace splitting
did not remove the remaining disagreement. Copper LVS suppresses plane opens;
it cannot be used as independent proof for these contacts. Tracked in
https://github.com/2AMLogic/kicad-tools/issues/5061. Native DRC remains the
connectivity authority for this development checkpoint; the disagreement
is retained as a release blocker.

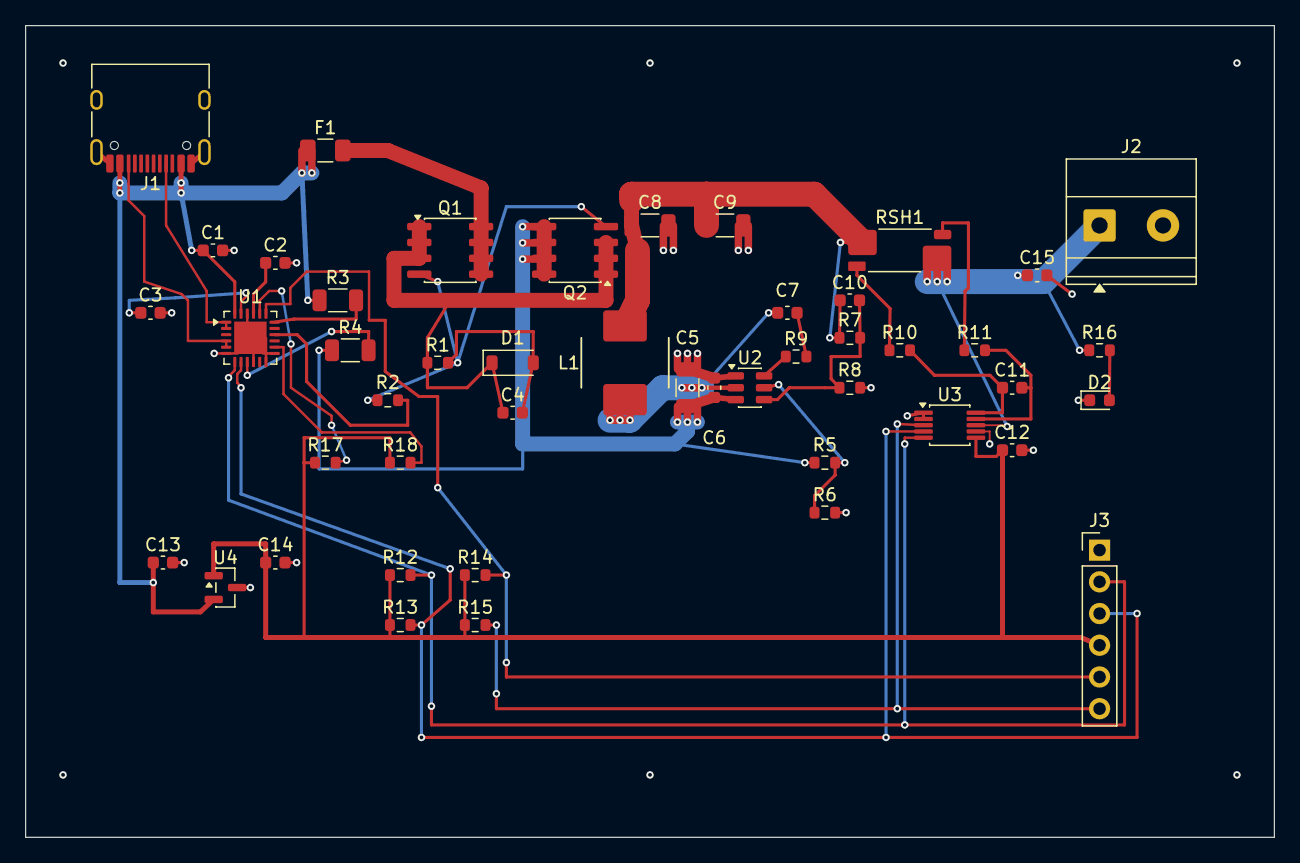
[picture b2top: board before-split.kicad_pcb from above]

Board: 4 copper layers, 100.0 x 65.0 mm, 47 parts (0 on the bottom side), 32 nets.

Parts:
C1, C13: 1u 50V; C_0603_1608Metric
C2, C3, C14, C15: 1u 16V; C_0603_1608Metric
C4: 4.7n 50V; C_0603_1608Metric
C5: 10u 50V; C_1206_3216Metric
C6, C7, C11, C12: 100n 50V; C_0603_1608Metric
C8, C9: 22u 25V; C_1206_3216Metric
C10: 75p C0G; C_0603_1608Metric
D1: 12V; D_SOD-123
D2: OUTPUT; LED_0603_1608Metric
F1: 2A 32V; Fuse_1206_3216Metric
J1: USB-C PD INPUT; USB_C_Receptacle_HRO_TYPE-C-31-M-12
J2: 5V OUTPUT; TerminalBlock_Phoenix_MKDS-1,5-2-5.08_1x02_P5.08mm_Horizont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
J3: I2C HOST 3V3; PinHeader_1x06_P2.54mm_Vertical
L1: 10uH; SRP7050TA
Q1, Q2: AO4407A; SOIC-8_3.9x4.9mm_P1.27mm
R1, R6: 100k; R_0603_1608Metric
R2, R14, R15, R17, R18: 10k; R_0603_1608Metric
R3, R4: 1k; R_1206_3216Metric
R5: 680k; R_0603_1608Metric
R7: 100k 0.1%; R_0603_1608Metric
R8: 13.3k 0.1%; R_0603_1608Metric
R9: 49.9; R_0603_1608Metric
R10, R11: 10; R_0603_1608Metric
R12, R13: 4.7k; R_0603_1608Metric
R16: 2.2k; R_0603_1608Metric
RSH1: 10m 1% 1W; R_Shunt_Vishay_WSK2512_6332Metric_T1.19mm
U1: STUSB4500QTR; QFN-24-1EP_4x4mm_P0.5mm_EP2.6x2.6mm
U2: TPS54302DDCR; TSOT-23-6
U3: INA226AIDGSR; MSOP-10_3x3mm_P0.5mm
U4: TLV76033DBZR; SOT-23

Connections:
+3V3: C12.1, C14.1, J3.4, R12.1, R13.1, R14.1, R15.1, R17.1, R18.1, U3.6, U4.1
+5V_OUT: C15.1, J2.1, R16.1, RSH1.4, U3.8
BOOT: R9.1, U2.6
BOOT_CAP: C7.1, R9.2
BUCK_EN: R5.2, R6.1, U2.5
CC1: J1.A5, U1.1, U1.2
CC2: J1.B5, U1.4, U1.5
DISCHARGE: R4.2, U1.9
FB: C10.2, R7.2, R8.1, U2.4
GND: C1.2, C2.2, C3.2, C5.2, C6.2, C8.2, C9.2, C12.2, C13.2, C14.2, C15.2, D2.1, J1.A1, J1.A12, J1.B1, J1.B12, J1.SH, J2.2, J3.1, R6.2, R8.2, U1.6, U1.10, U1.12, U1.13, U1.22, U1.25, U2.1, U3.1, U3.2, U3.7, U4.3
KELVIN_N: R11.1, RSH1.3
KELVIN_P: R10.1, RSH1.2
LED_A: D2.2, R16.2
MON_ALERT: J3.6, R15.2, U3.3
PD_ALERT: J3.5, R14.2, U1.19
PD_OK2: R17.2, U1.20
PD_OK3: R18.2, U1.14
PMOS_GATE: C4.2, D1.2, Q1.4, Q2.4, R1.2, R2.1
PMOS_SOURCE: C4.1, D1.1, Q1.1, Q1.2, Q1.3, Q2.1, Q2.2, Q2.3, R1.1
SCL: J3.2, R12.2, U1.7, U3.5
SDA: J3.3, R13.2, U1.8, U3.4
SENSE_N: C11.2, R11.2, U3.9
SENSE_P: C11.1, R10.2, U3.10
SINK_GATE: R2.2, U1.16
SW: C7.2, L1.1, U2.2
VBUS_FUSED: F1.2, Q1.5, Q1.6, Q1.7, Q1.8
VBUS_RAW: C1.1, C13.1, F1.1, J1.A4, J1.A9, J1.B4, J1.B9, R3.1, U1.24, U4.2
VBUS_SENSE: R3.2, U1.18
VIN: C5.1, C6.1, Q2.5, Q2.6, Q2.7, Q2.8, R4.1, R5.1, U2.3
VOUT_PRE: C8.1, C9.1, C10.1, L1.2, R7.1, RSH1.1
VREG_1V2: C2.1, U1.21
VREG_2V7: C3.1, U1.23
